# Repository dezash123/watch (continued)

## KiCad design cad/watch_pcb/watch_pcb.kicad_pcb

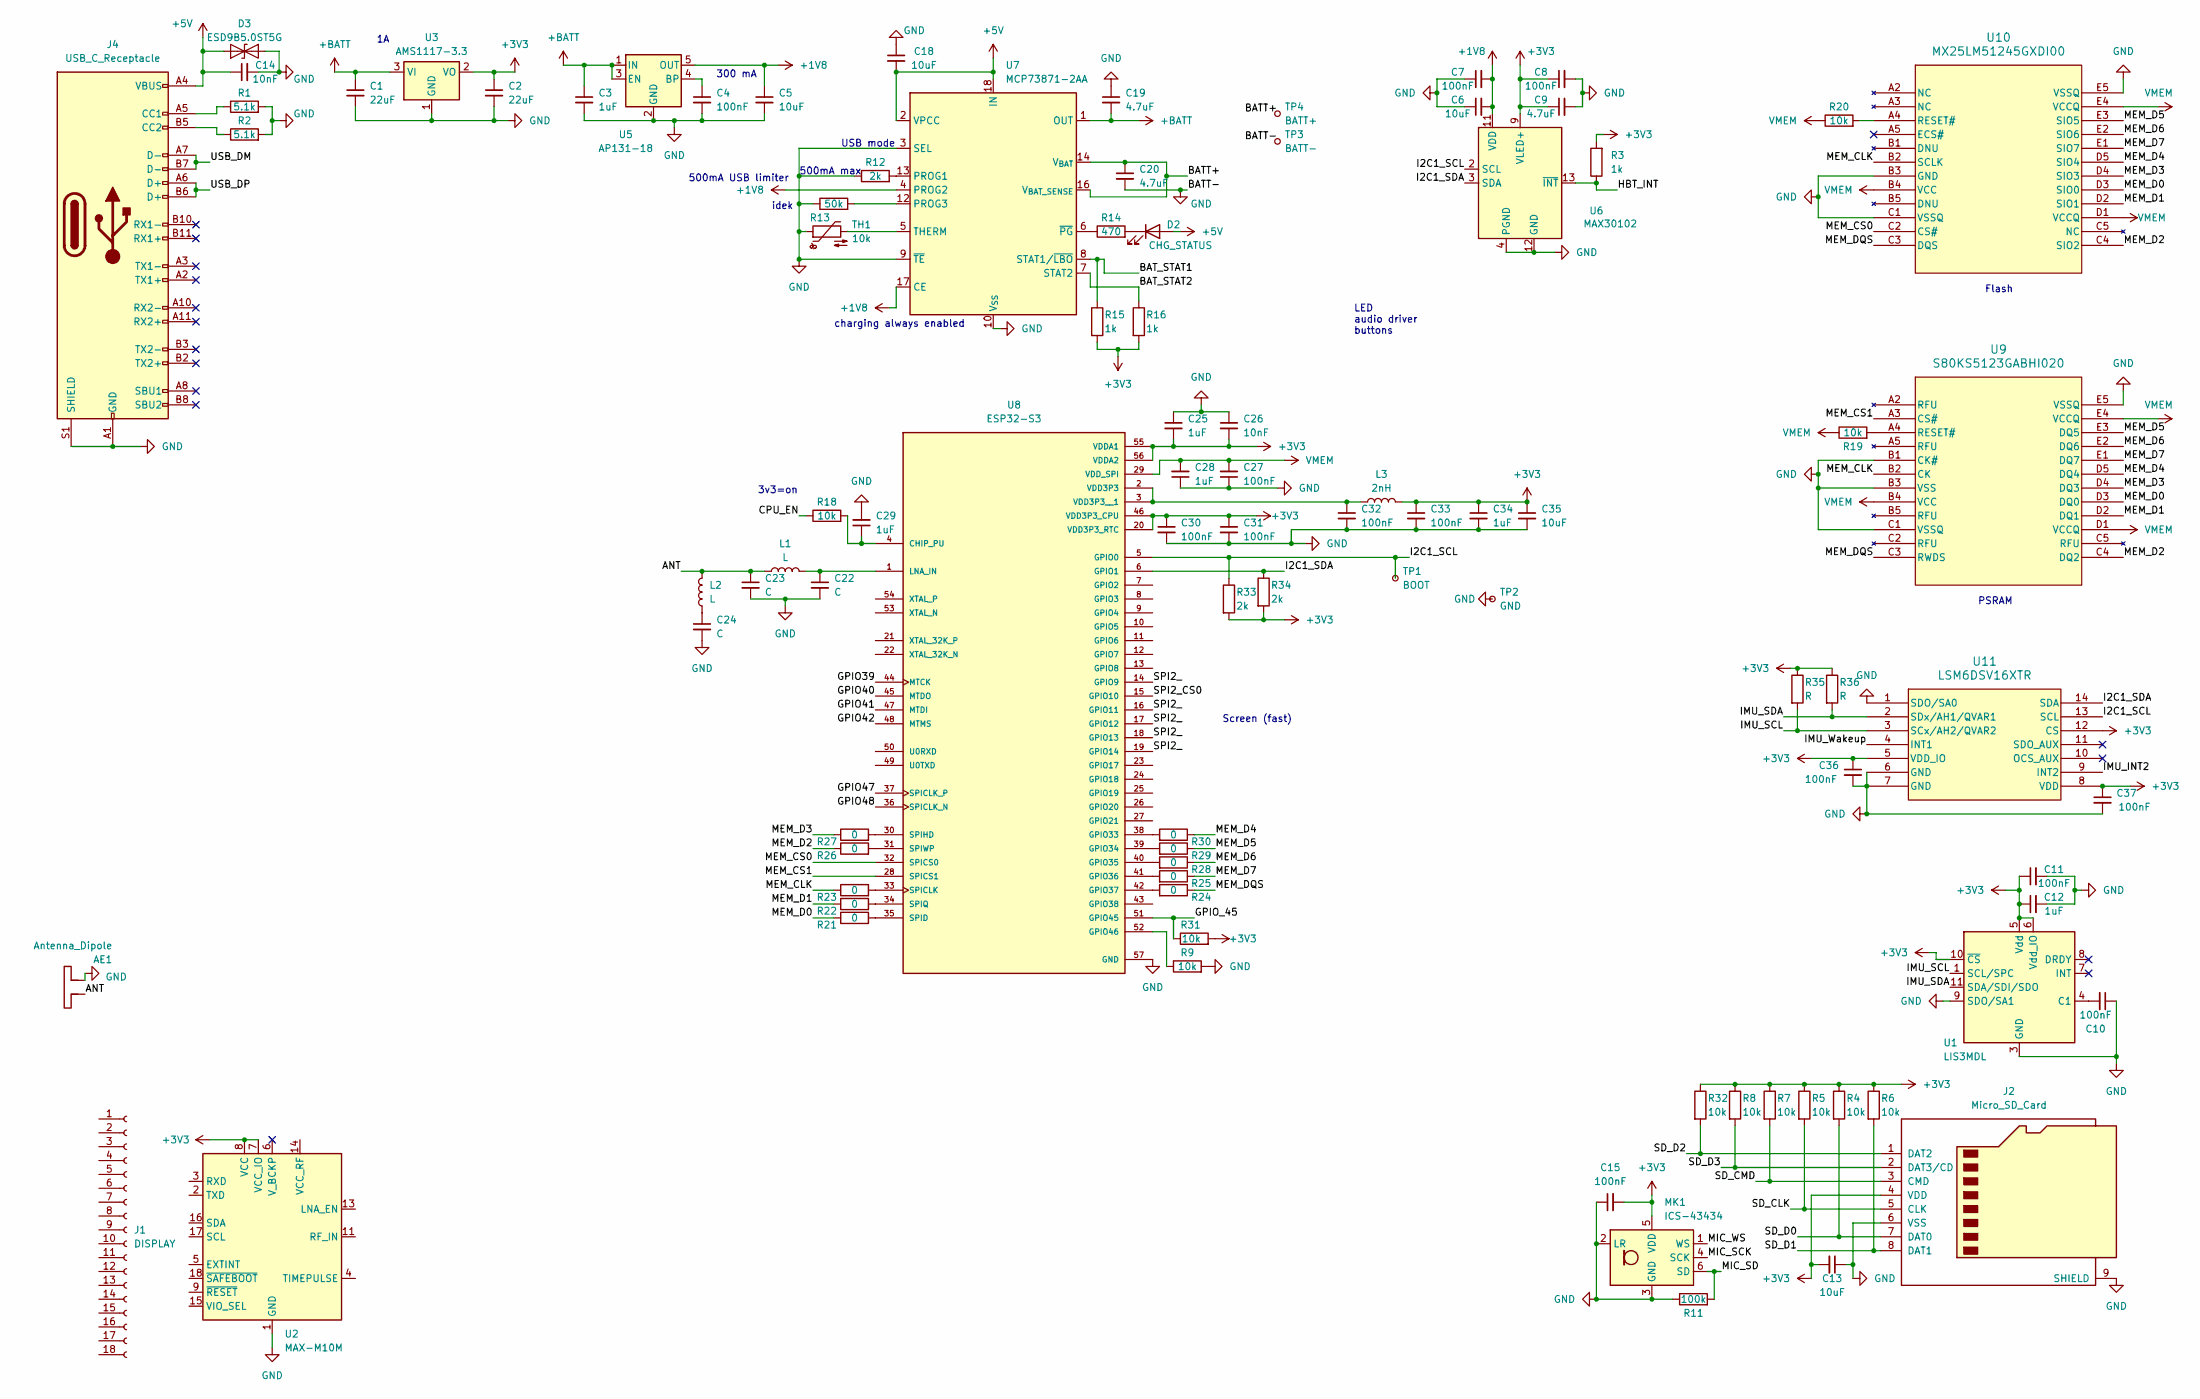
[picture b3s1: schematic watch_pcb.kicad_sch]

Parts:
AE1: Antenna_Dipole; Texas_SWRA117D_2.4GHz_Right
C1, C2: 22uF; C_0603_1608Metric
C3, C12, C25, C28, C29, C34: 1uF; C_0402_1005Metric
C4, C7, C8, C10, C11, C15, C27, C30, C31, C32, C33, C36, C37: 100nF; C_0201_0603Metric
C5, C6, C13, C18, C35: 10uF; C_0402_1005Metric
C9, C19, C20: 4.7uF; C_0603_1608Metric
C14, C26: 10nF; C_0201_0603Metric
C22, C23, C24: C
D2: CHG_STATUS
D3: ESD9B5.0ST5G; D_SOD-923
J1: DISPLAY; Hirose_FH12-18S-0.5SH_1x18-1MP_P0.50mm_Horizontal
J2: Micro_SD_Card; MOLEX_503398-1892
J4: USB_C_Receptacle; JAE_DX07B024JJ1R1500
L1, L2: L
L3: 2nH
MK1: ICS-43434; InvenSense_ICS-43434-6_3.5x2.65mm
R1, R2: 5.1k; R_0402_1005Metric
R3, R15, R16: 1k; R_0402_1005Metric
R4, R5, R6, R7, R8, R9, R18, R19, R20, R31, R32: 10k; R_0402_1005Metric
R11: 100k; R_0402_1005Metric
R12, R33, R34: 2k; R_0402_1005Metric
R13: 50k; R_0402_1005Metric
R14: 470; R_0402_1005Metric
R21, R22, R23, R24, R25, R26, R27, R28, R29, R30: 0; R_0402_1005Metric
R35, R36: R; R_0402_1005Metric
TH1: 10k
TP1: BOOT; TestPoint_Pad_D2.0mm
TP2: GND; TestPoint_Pad_2.0x2.0mm
TP3: BATT-; TestPoint_Pad_2.5x2.5mm
TP4: BATT+; TestPoint_Pad_D2.5mm
U1: LIS3MDL; LGA-12_2x2mm_P0.5mm
U2: MAX-M10M; ublox_MAX
U3: AMS1117-3.3; SOT-223-3_TabPin2
U5: AP131-18; SOT-23-5
U6: MAX30102; Maxim_OLGA-14_3.3x5.6mm_P0.8mm
U7: MCP73871-2AA; QFN-20-1EP_4x4mm_P0.5mm_EP2.5x2.5mm
U8: ESP32-S3; IC_ESP32-S3; PARTREV v1.2
U9: S80KS5123GABHI020; PG-BGA-24-801
U10: MX25LM51245GXDI00; CSP24_6X8X1.2_MAC
U11: LSM6DSV16XTR; LGA14L_LSM6_STM

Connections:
+1V8: C5.1, C6.2, C7.2, U5.5 (OUT), U6.11 (VDD), U7.4 (PROG2), U7.17 (CE)
+3V3: C2.1, C8.1, C9.1, C11.1, C12.1, C13.2, C15.2, C25.2, C26.2, C30.1, C31.1, C33.1, C34.1, C35.1, C36.1, C37.1, J2.4 (VDD), L3.2, MK1.5 (VDD), R3.2, R4.1, R5.1, R6.1, R7.1, R8.1, R15.2, R16.2, R31.2, R32.1, R33.2, R34.2, R35.1, R36.1, U1.5 (Vdd), U1.6 (Vdd_IO), U1.10 (~CS), U2.7 (VCC_IO), U2.8 (VCC), U3.2 (VO), U6.9 (VLED+), U6.10 (VLED+), U8.20 (VDD3P3_RTC), U8.46 (VDD3P3_CPU), U8.55 (VDDA1), U8.56 (VDDA2), U11.5 (VDD_IO), U11.8 (VDD), U11.12 (CS)
+5V: C14.1, C18.2, D2.2 (A), D3.1 (A1), J4.A4 (VBUS), J4.A9 (VBUS), J4.B4 (VBUS), J4.B9 (VBUS), U7.2 (VPCC), U7.18 (IN), U7.19 (IN)
+BATT: C1.1, C3.1, C19.2, U3.3 (VI), U5.1 (IN), U5.3 (EN), U7.1 (OUT), U7.20 (OUT)
/ANT: AE1.1, C23.1, L1.1, L2.2
/BATT+: C20.1, TP4.1, U7.14 (V_{BAT}), U7.15 (V_{BAT}), U7.16 (V_{BAT_SENSE})
/BAT_STAT1: R15.1, U7.8 (STAT1/~LBO)
/BAT_STAT2: R16.1, U7.7 (STAT2)
/CPU_EN: R18.1
/GPIO39: U8.44 (MTCK)
/GPIO40: U8.45 (MTDO)
/GPIO41: U8.47 (MTDI)
/GPIO42: U8.48 (MTMS)
/GPIO47: U8.37 (SPICLK_P)
/GPIO48: U8.36 (SPICLK_N)
/GPIO_45: R31.1, U8.51 (GPIO45)
/HBT_INT: R3.1, U6.13 (~INT)
/I2C1_SCL: R33.1, TP1.1, U6.2 (SCL), U8.5 (GPIO0), U11.13 (SCL)
/I2C1_SDA: R34.1, U6.3 (SDA), U8.6 (GPIO1), U11.14 (SDA)
/IMU_INT2: U11.9 (INT2)
/IMU_SCL: R35.2, U1.1 (SCL/SPC), U11.3 (SCx/AH2/QVAR2)
/IMU_SDA: R36.2, U1.11 (SDA/SDI/SDO), U11.2 (SDx/AH1/QVAR1)
/IMU_Wakeup: U11.4 (INT1)
/MEM_CLK: R23.1, U9.B2 (CK), U10.B2 (SCLK)
/MEM_CS0: U8.32 (SPICS0), U10.C2 (CS#)
/MEM_CS1: U8.28 (SPICS1), U9.A3 (CS#)
/MEM_D0: R21.1, U9.D3 (DQ0), U10.D3 (SIO0)
/MEM_D1: R22.1, U9.D2 (DQ1), U10.D2 (SIO1)
/MEM_D2: R26.1, U9.C4 (DQ2), U10.C4 (SIO2)
/MEM_D3: R27.1, U9.D4 (DQ3), U10.D4 (SIO3)
/MEM_D4: R30.1, U9.D5 (DQ4), U10.D5 (SIO4)
/MEM_D5: R29.1, U9.E3 (DQ5), U10.E3 (SIO5)
/MEM_D6: R28.1, U9.E2 (DQ6), U10.E2 (SIO6)
/MEM_D7: R25.1, U9.E1 (DQ7), U10.E1 (SIO7)
/MEM_DQS: R24.1, U9.C3 (RWDS), U10.C3 (DQS)
/MIC_SCK: MK1.4 (SCK)
/MIC_SD: MK1.6 (SD), R11.2
/MIC_WS: MK1.1 (WS)
/SD_CLK: J2.5 (CLK), R5.2
/SD_CMD: J2.3 (CMD), R7.2
/SD_D0: J2.7 (DAT0), R4.2
/SD_D1: J2.8 (DAT1), R6.2
/SD_D2: J2.1 (DAT2), R32.2
/SD_D3: J2.2 (DAT3/CD), R8.2
/SPI2_: U8.14 (GPIO9), U8.16 (GPIO11), U8.17 (GPIO12), U8.18 (GPIO13), U8.19 (GPIO14)
/SPI2_CS0: U8.15 (GPIO10)
/USB_DM: J4.A7 (D-), J4.B7 (D-)
/USB_DP: J4.A6 (D+), J4.B6 (D+)
GND: AE1.2, C1.2, C2.2, C3.2, C4.2, C5.2, C6.1, C7.1, C8.2, C9.2, C10.1, C11.2, C12.2, C13.1, C14.2, C15.1, C18.1, C19.1, C20.2, C22.2, C23.2, C24.2, C25.1, C26.1, C27.1, C28.1, C29.2, C30.2, C31.2, C32.2, C33.2, C34.2, C35.2, C36.2, C37.2, D3.2 (A2), J2.6 (VSS), J2.9 (SHIELD), J4.A1 (GND), J4.A12 (GND), J4.B1 (GND), J4.B12 (GND), J4.S1 (SHIELD), MK1.2 (LR), MK1.3 (GND), R1.2, R2.2, R9.2, R11.1, R12.1, R13.1, TH1.1, TP2.1, TP3.1, U1.2 (GND), U1.3 (GND), U1.9 (SDO/SA1), U1.12 (GND), U2.1 (GND), U2.10 (GND), U2.12 (GND), U3.1 (GND), U5.2 (GND), U6.4 (PGND), U6.12 (GND), U7.3 (SEL), U7.9 (~TE), U7.10 (V_{SS}), U7.11 (V_{SS}), U7.21 (V_{SS}), U8.57 (GND), U9.B1 (CK#), U9.B3 (VSS), U9.C1 (VSSQ), U9.E5 (VSSQ), U10.B3 (GND), U10.C1 (VSSQ), U10.E5 (VSSQ), U11.1 (SDO/SA0), U11.6 (GND), U11.7 (GND)
unnamed: C24.1, L2.1
unnamed: D2.1 (K), R14.2
unnamed: J4.A5 (CC1), R1.1
unnamed: J4.B5 (CC2), R2.1
unnamed: C10.2, U1.4 (C1)
unnamed: C4.1, U5.4 (BP)
unnamed: R12.2, U7.13 (PROG1)
unnamed: R13.2, U7.12 (PROG3)
unnamed: TH1.2, U7.5 (THERM)
unnamed: R14.1, U7.6 (~PG)
unnamed: C29.1, R18.2, U8.4 (CHIP_PU)
unnamed: R30.2, U8.38 (GPIO33)
unnamed: R29.2, U8.39 (GPIO34)
unnamed: R28.2, U8.40 (GPIO35)
unnamed: R25.2, U8.41 (GPIO36)
unnamed: R24.2, U8.42 (GPIO37)
unnamed: R9.1, U8.52 (GPIO46)
unnamed: C22.1, L1.2, U8.1 (LNA_IN)
unnamed: R23.2, U8.33 (SPICLK)
unnamed: R21.2, U8.35 (SPID)
unnamed: R27.2, U8.30 (SPIHD)
unnamed: R22.2, U8.34 (SPIQ)
unnamed: R26.2, U8.31 (SPIWP)
unnamed: C32.1, L3.1, U8.2 (VDD3P3), U8.3 (VDD3P3__1)
unnamed: R19.2, U9.A4 (RESET#)
unnamed: R20.2, U10.A4 (RESET#)
VMEM: C27.2, C28.2, R19.1, R20.1, U8.29 (VDD_SPI), U9.B4 (VCC), U9.D1 (VCCQ), U9.E4 (VCCQ), U10.B4 (VCC), U10.D1 (VCCQ), U10.E4 (VCCQ)

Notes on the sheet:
USB mode
300 mA
500mA USB limiter
Screen (fast)
idek
Flash
charging always enabled
500mA max
3v3=on
PSRAM
LED audio driver buttons

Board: 4 copper layers, 85 parts (18 on the bottom side), 59 nets, no tracks yet.

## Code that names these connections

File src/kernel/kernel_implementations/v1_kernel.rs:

use async_trait::async_trait;
use alloc::boxed::Box;
use embassy_embedded_hal::shared_bus::asynch::i2c::I2cDevice;
use embassy_sync::{blocking_mutex::raw::NoopRawMutex, mutex::Mutex};
use esp_hal::{clock::ClockControl, gpio::IO, i2c::I2C, peripherals::{Peripherals, I2C0, I2C1}, Async};
use fugit::RateExtU32;
use static_cell::StaticCell;
use esp_hal::prelude::_esp_hal_system_SystemExt;

use crate::os::kernel::{drivers::{display::pcf8574t::Pcf8574t, Device}, Kernel, KernelError};

pub static I2C0_BUS: StaticCell<Mutex<NoopRawMutex, I2C<I2C0, Async>>> = StaticCell::new();
pub static I2C1_BUS: StaticCell<Mutex<NoopRawMutex, I2C<I2C1, Async>>> = StaticCell::new();

pub struct V1Kernel {
}

#[async_trait(?Send)]
impl Kernel for V1Kernel {
    async fn new() -> Self {
        let peripherals = Peripherals::take();
        let system = peripherals.SYSTEM.split();
        let cocks = ClockControl::max(system.clock_control).freeze();
        let io = IO::new(peripherals.GPIO, peripherals.IO_MUX);

        let i2c0_scl = io.pins.gpio0;
        let i2c0_sda = io.pins.gpio1;
        let i2c1_scl = io.pins.gpio2;
        let i2c1_sda = io.pins.gpio3;

        let i2c0 = I2C::new_async(
            peripherals.I2C0,
            i2c0_sda,
            i2c0_scl,
            400u32.kHz(),
            &cocks,
        );
        let i2c1 = I2C::new_async(
            peripherals.I2C1,
            i2c1_sda,
            i2c1_scl,
            400u32.kHz(),
            &cocks,
        );

        let i2c0_bus = Mutex::new(i2c0);
        let i2c0_bus = I2C0_BUS.init(i2c0_bus);
        let i2c1_bus = Mutex::new(i2c1);
        let i2c1_bus = I2C1_BUS.init(i2c1_bus);

        let text_display = Pcf8574t::new(I2cDevice::new(i2c0_bus)).await;

        Self {
        }
    }
    async fn manage_inputs(&mut self) -> Result<(), KernelError> {
        Ok(())
    }
    async fn manage_outputs(&mut self) -> Result<(), KernelError> {
        Ok(())
    }
}

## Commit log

2024-01-20 pcb stuff
2024-01-20 more
2024-04-01 idk some stuff
2024-05-11 refactoring
2024-05-11 refactoring more
2024-05-12 i think ik what im doing (i dont)
2024-05-12 everything will be async
2024-05-13 Wait, it's all async?
2024-05-19 too much to list
2024-05-19 nevermind??
2024-06-03 move pcb to separate repo
2024-06-05 custom symbols moar
2024-06-05 might switch to c/++ :'(
2024-06-08 display started
2024-06-13 finished schematic, verifying design and doing daughter board
2024-06-18 both??
2024-06-30 nearly done with schematic i thinks
2024-07-04 reorganization
2024-07-04 basically done probably
2024-07-04 initial empty commit
2024-07-04 switching to one repo
2024-07-04 switching to single repo
2024-07-04 Move os files into subdir
2024-07-04 Move pcb files into subdir
2024-07-08 think i have good organization ideas now maybe
2024-07-17 git is a tool for torture
2024-07-30 finished pcb layout
2024-07-31 switching to 6 layer
2024-09-26 made many changes, maybe switching to stm tho
2024-09-26 initial stm commit
2024-10-17 things
2024-10-17 wrote a bunch then accidentally rm'd it :'(
2024-10-17 commit paranoia
2024-10-18 removed the bad things
2024-10-18 removed more bad things
2024-10-29 changing to arduino code for display driver
2024-10-29 what i said before
2024-10-29 mreged
2024-10-29 basically the same but more constants
2024-10-31 i think rtic is just not there yet :( Switching back to embassy
2024-10-31 embassy seems to work
2025-03-08 returning and reorganizing
